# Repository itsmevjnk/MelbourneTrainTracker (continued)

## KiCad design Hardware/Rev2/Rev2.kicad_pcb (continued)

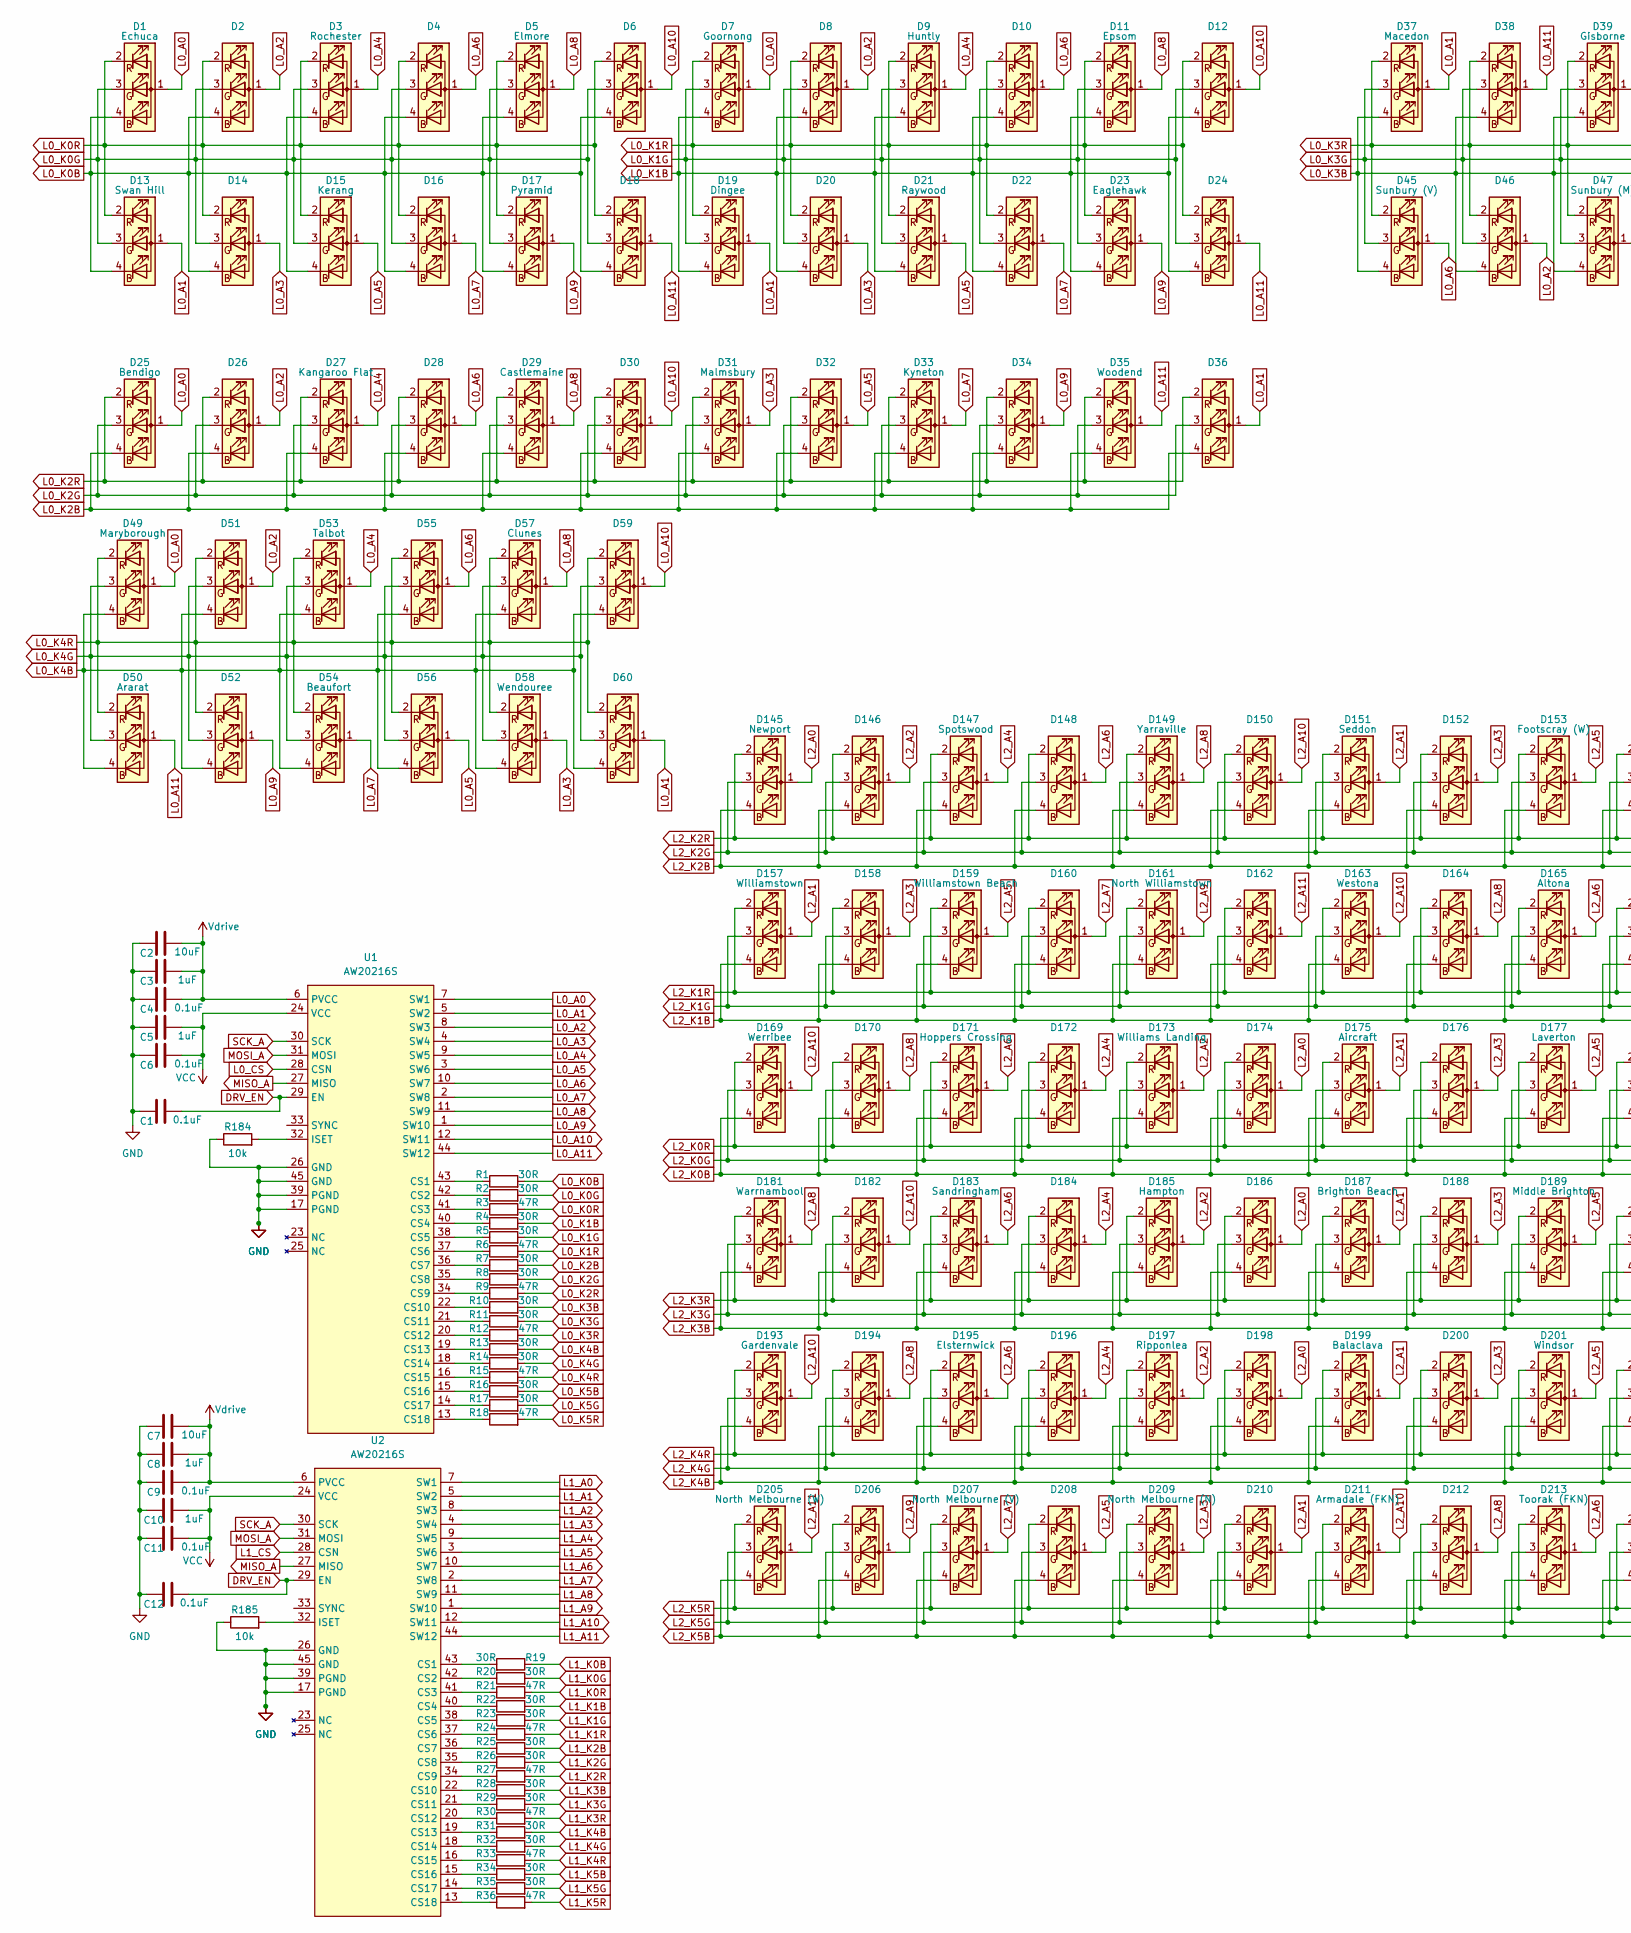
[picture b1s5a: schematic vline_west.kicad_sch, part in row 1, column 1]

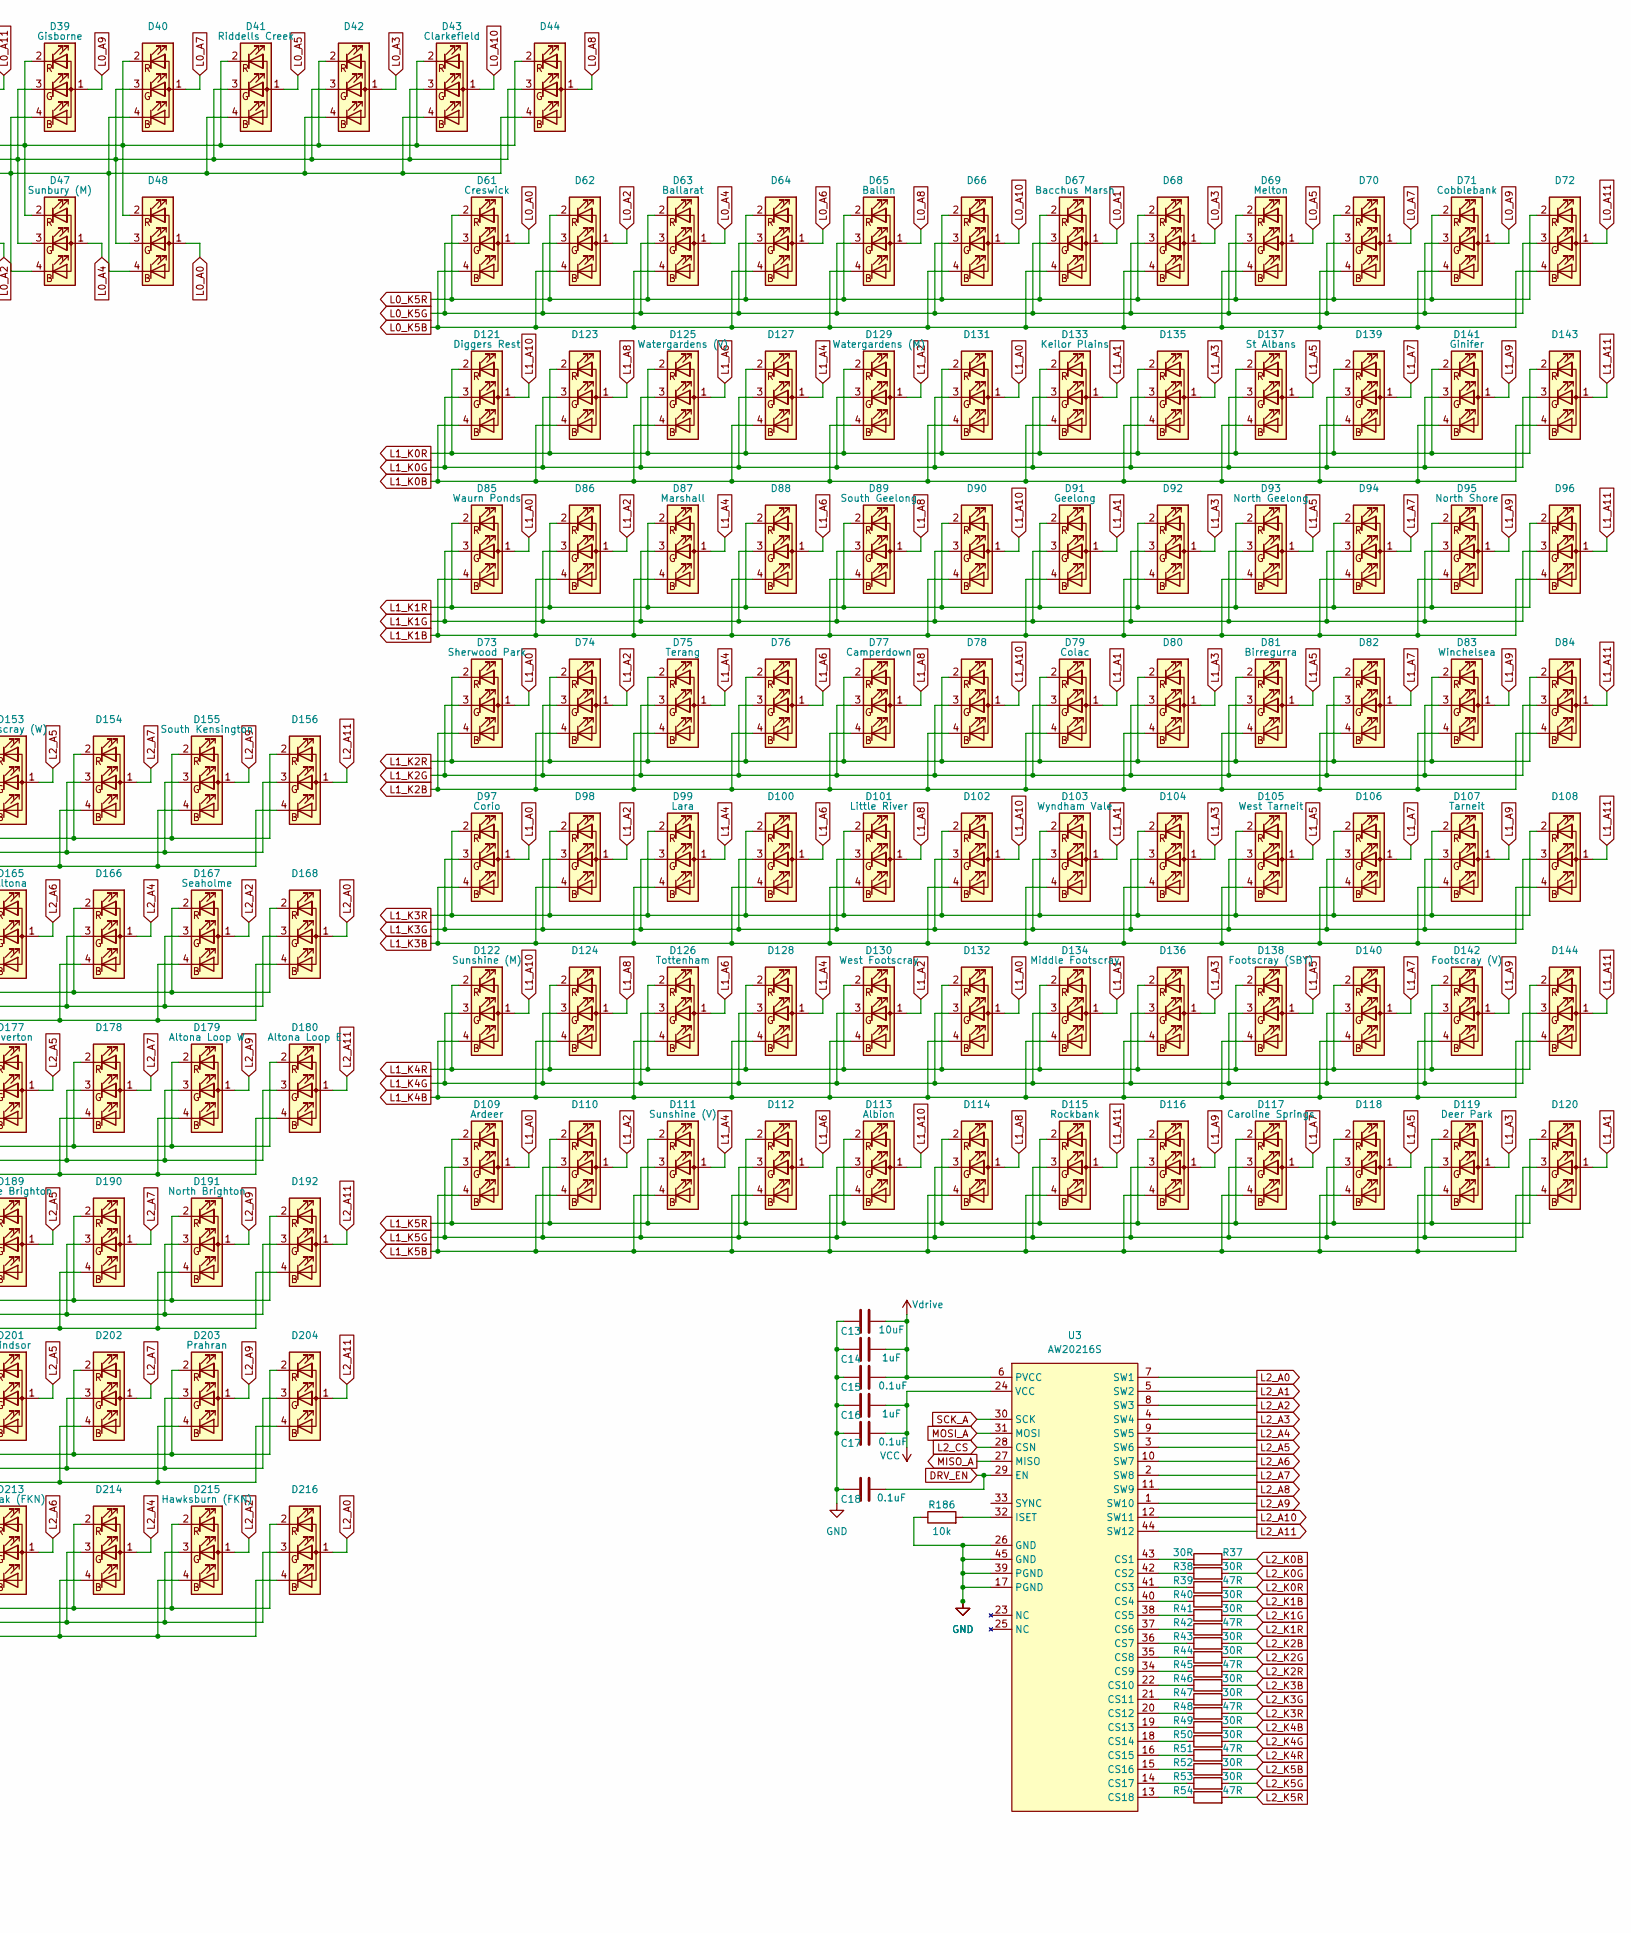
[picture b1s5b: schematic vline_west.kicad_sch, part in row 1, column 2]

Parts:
C1, C4, C6, C9, C11, C12, C15, C17, C18: 0.1uF; C_0603_1608Metric_Pad1.08x0.95mm_HandSolder; MPN C14663
C2, C7, C13: 10uF; C_0805_2012Metric_Pad1.18x1.45mm_HandSolder; MPN C380332
C3, C5, C8, C10, C14, C16: 1uF; C_0603_1608Metric_Pad1.08x0.95mm_HandSolder; MPN C6119849
D1, D2, D3, D4, D5, D6, D7, D8, D9, D10, D11, D12, D13, D14, D15, D16, D17, D18, D19, D20, D21, D22, D23, D24, D25, D26, D27, D28, D29, D30, D31, D32, D33, D34, D35, D36, D37, D38, D39, D40, D41, D42, D43, D44, D45, D46, D47, D48, D49, D50, D51, D52, D53, D54, D55, D56, D57, D58, D59, D60, D61, D62, D63, D64, D65, D66, D67, D68, D69, D70, D71, D72, D73, D74, D75, D76, D77, D78, D79, D80, D81, D82, D83, D84, D85, D86, D87, D88, D89, D90, D91, D92, D93, D94, D95, D96, D97, D98, D99, D100, D101, D102, D103, D104, D105, D106, D107, D108, D109, D110, D111, D112, D113, D114, D115, D116, D117, D118, D119, D120, D121, D122, D123, D124, D125, D126, D127, D128, D129, D130, D131, D132, D133, D134, D135, D136, D137, D138, D139, D140, D141, D142, D143, D144, D145, D146, D147, D148, D149, D150, D151, D152, D153, D154, D155, D156, D157, D158, D159, D160, D161, D162, D163, D164, D165, D166, D167, D168, D169, D170, D171, D172, D173, D174, D175, D176, D177, D178, D179, D180, D181, D182, D183, D184, D185, D186, D187, D188, D189, D190, D191, D192, D193, D194, D195, D196, D197, D198, D199, D200, D201, D202, D203, D204, D205, D206, D207, D208, D209, D210, D211, D212, D213, D214, D215, D216: XL-B1010RGBT-HF; LED_RGB_Xinglight-1010; MPN C22464515
R1, R2, R4, R5, R7, R8, R10, R11, R13, R14, R16, R17, R19, R20, R22, R23, R25, R26, R28, R29, R31, R32, R34, R35, R37, R38, R40, R41, R43, R44, R46, R47, R49, R50, R52, R53: 30R; R_0805_2012Metric_Pad1.20x1.40mm_HandSolder
R3, R6, R9, R12, R15, R18, R21, R24, R27, R30, R33, R36, R39, R42, R45, R48, R51, R54: 47R; R_0805_2012Metric_Pad1.20x1.40mm_HandSolder
R184, R185, R186: 10k; R_0603_1608Metric_Pad0.98x0.95mm_HandSolder; MPN C15401
U1, U2, U3: AW20216S; QFN-44-1EP_5x5mm_P0.4mm_EP2.45x2.45mm; MPN C7385556

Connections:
+3.3V: C5.2, C6.2, C10.2, C11.2, C16.2, C17.2, U1.24 (VCC), U2.24 (VCC), U3.24 (VCC); also elsewhere on the board
+5V: C2.2, C3.2, C4.2, C7.2, C8.2, C9.2, C13.2, C14.2, C15.2, U1.6 (PVCC), U2.6 (PVCC), U3.6 (PVCC); also elsewhere on the board
DRV_EN: C1.2, C12.2, C18.2, U1.29 (EN), U2.29 (EN), U3.29 (EN); also elsewhere on the board
GND: C1.1, C2.1, C3.1, C4.1, C5.1, C6.1, C7.1, C8.1, C9.1, C10.1, C11.1, C12.1, C13.1, C14.1, C15.1, C16.1, C17.1, C18.1, R184.1, R185.1, R186.1, U1.17 (PGND), U1.26 (GND), U1.39 (PGND), U1.45 (GND), U2.17 (PGND), U2.26 (GND), U2.39 (PGND), U2.45 (GND), U3.17 (PGND), U3.26 (GND), U3.39 (PGND), U3.45 (GND); also elsewhere on the board
L0_A0: D1.1 (A), D7.1 (A), D25.1 (A), D48.1 (A), D49.1 (A), D61.1 (A), U1.7 (SW1)
L0_A1: D13.1 (A), D19.1 (A), D36.1 (A), D37.1 (A), D60.1 (A), D67.1 (A), U1.5 (SW2)
L0_A2: D2.1 (A), D8.1 (A), D26.1 (A), D46.1 (A), D51.1 (A), D62.1 (A), U1.8 (SW3)
L0_A3: D14.1 (A), D20.1 (A), D31.1 (A), D42.1 (A), D58.1 (A), D68.1 (A), U1.4 (SW4)
L0_A4: D3.1 (A), D9.1 (A), D27.1 (A), D47.1 (A), D53.1 (A), D63.1 (A), U1.9 (SW5)
L0_A5: D15.1 (A), D21.1 (A), D32.1 (A), D41.1 (A), D56.1 (A), D69.1 (A), U1.3 (SW6)
L0_A6: D4.1 (A), D10.1 (A), D28.1 (A), D45.1 (A), D55.1 (A), D64.1 (A), U1.10 (SW7)
L0_A7: D16.1 (A), D22.1 (A), D33.1 (A), D40.1 (A), D54.1 (A), D70.1 (A), U1.2 (SW8)
L0_A8: D5.1 (A), D11.1 (A), D29.1 (A), D44.1 (A), D57.1 (A), D65.1 (A), U1.11 (SW9)
L0_A9: D17.1 (A), D23.1 (A), D34.1 (A), D39.1 (A), D52.1 (A), D71.1 (A), U1.1 (SW10)
L0_A10: D6.1 (A), D12.1 (A), D30.1 (A), D43.1 (A), D59.1 (A), D66.1 (A), U1.12 (SW11)
L0_A11: D18.1 (A), D24.1 (A), D35.1 (A), D38.1 (A), D50.1 (A), D72.1 (A), U1.44 (SW12)
L0_CS: U1.28 (CSN); also elsewhere on the board
L0_K0B: D1.4 (BK), D2.4 (BK), D3.4 (BK), D4.4 (BK), D5.4 (BK), D6.4 (BK), D13.4 (BK), D14.4 (BK), D15.4 (BK), D16.4 (BK), D17.4 (BK), D18.4 (BK), R1.2
L0_K0G: D1.3 (GK), D2.3 (GK), D3.3 (GK), D4.3 (GK), D5.3 (GK), D6.3 (GK), D13.3 (GK), D14.3 (GK), D15.3 (GK), D16.3 (GK), D17.3 (GK), D18.3 (GK), R2.2
L0_K0R: D1.2 (RK), D2.2 (RK), D3.2 (RK), D4.2 (RK), D5.2 (RK), D6.2 (RK), D13.2 (RK), D14.2 (RK), D15.2 (RK), D16.2 (RK), D17.2 (RK), D18.2 (RK), R3.2
L0_K1B: D7.4 (BK), D8.4 (BK), D9.4 (BK), D10.4 (BK), D11.4 (BK), D12.4 (BK), D19.4 (BK), D20.4 (BK), D21.4 (BK), D22.4 (BK), D23.4 (BK), D24.4 (BK), R4.2
L0_K1G: D7.3 (GK), D8.3 (GK), D9.3 (GK), D10.3 (GK), D11.3 (GK), D12.3 (GK), D19.3 (GK), D20.3 (GK), D21.3 (GK), D22.3 (GK), D23.3 (GK), D24.3 (GK), R5.2
L0_K1R: D7.2 (RK), D8.2 (RK), D9.2 (RK), D10.2 (RK), D11.2 (RK), D12.2 (RK), D19.2 (RK), D20.2 (RK), D21.2 (RK), D22.2 (RK), D23.2 (RK), D24.2 (RK), R6.2
L0_K2B: D25.4 (BK), D26.4 (BK), D27.4 (BK), D28.4 (BK), D29.4 (BK), D30.4 (BK), D31.4 (BK), D32.4 (BK), D33.4 (BK), D34.4 (BK), D35.4 (BK), D36.4 (BK), R7.2
L0_K2G: D25.3 (GK), D26.3 (GK), D27.3 (GK), D28.3 (GK), D29.3 (GK), D30.3 (GK), D31.3 (GK), D32.3 (GK), D33.3 (GK), D34.3 (GK), D35.3 (GK), D36.3 (GK), R8.2
L0_K2R: D25.2 (RK), D26.2 (RK), D27.2 (RK), D28.2 (RK), D29.2 (RK), D30.2 (RK), D31.2 (RK), D32.2 (RK), D33.2 (RK), D34.2 (RK), D35.2 (RK), D36.2 (RK), R9.2
L0_K3B: D37.4 (BK), D38.4 (BK), D39.4 (BK), D40.4 (BK), D41.4 (BK), D42.4 (BK), D43.4 (BK), D44.4 (BK), D45.4 (BK), D46.4 (BK), D47.4 (BK), D48.4 (BK), R10.2
L0_K3G: D37.3 (GK), D38.3 (GK), D39.3 (GK), D40.3 (GK), D41.3 (GK), D42.3 (GK), D43.3 (GK), D44.3 (GK), D45.3 (GK), D46.3 (GK), D47.3 (GK), D48.3 (GK), R11.2
L0_K3R: D37.2 (RK), D38.2 (RK), D39.2 (RK), D40.2 (RK), D41.2 (RK), D42.2 (RK), D43.2 (RK), D44.2 (RK), D45.2 (RK), D46.2 (RK), D47.2 (RK), D48.2 (RK), R12.2
L0_K4B: D49.4 (BK), D50.4 (BK), D51.4 (BK), D52.4 (BK), D53.4 (BK), D54.4 (BK), D55.4 (BK), D56.4 (BK), D57.4 (BK), D58.4 (BK), D59.4 (BK), D60.4 (BK), R13.2
L0_K4G: D49.3 (GK), D50.3 (GK), D51.3 (GK), D52.3 (GK), D53.3 (GK), D54.3 (GK), D55.3 (GK), D56.3 (GK), D57.3 (GK), D58.3 (GK), D59.3 (GK), D60.3 (GK), R14.2
L0_K4R: D49.2 (RK), D50.2 (RK), D51.2 (RK), D52.2 (RK), D53.2 (RK), D54.2 (RK), D55.2 (RK), D56.2 (RK), D57.2 (RK), D58.2 (RK), D59.2 (RK), D60.2 (RK), R15.2
L0_K5B: D61.4 (BK), D62.4 (BK), D63.4 (BK), D64.4 (BK), D65.4 (BK), D66.4 (BK), D67.4 (BK), D68.4 (BK), D69.4 (BK), D70.4 (BK), D71.4 (BK), D72.4 (BK), R16.2
L0_K5G: D61.3 (GK), D62.3 (GK), D63.3 (GK), D64.3 (GK), D65.3 (GK), D66.3 (GK), D67.3 (GK), D68.3 (GK), D69.3 (GK), D70.3 (GK), D71.3 (GK), D72.3 (GK), R17.2
L0_K5R: D61.2 (RK), D62.2 (RK), D63.2 (RK), D64.2 (RK), D65.2 (RK), D66.2 (RK), D67.2 (RK), D68.2 (RK), D69.2 (RK), D70.2 (RK), D71.2 (RK), D72.2 (RK), R18.2
L1_A0: D73.1 (A), D85.1 (A), D97.1 (A), D109.1 (A), D131.1 (A), D132.1 (A), U2.7 (SW1)
L1_A1: D79.1 (A), D91.1 (A), D103.1 (A), D120.1 (A), D133.1 (A), D134.1 (A), U2.5 (SW2)
L1_A2: D74.1 (A), D86.1 (A), D98.1 (A), D110.1 (A), D129.1 (A), D130.1 (A), U2.8 (SW3)
L1_A3: D80.1 (A), D92.1 (A), D104.1 (A), D119.1 (A), D135.1 (A), D136.1 (A), U2.4 (SW4)
L1_A4: D75.1 (A), D87.1 (A), D99.1 (A), D111.1 (A), D127.1 (A), D128.1 (A), U2.9 (SW5)
L1_A5: D81.1 (A), D93.1 (A), D105.1 (A), D118.1 (A), D137.1 (A), D138.1 (A), U2.3 (SW6)
L1_A6: D76.1 (A), D88.1 (A), D100.1 (A), D112.1 (A), D125.1 (A), D126.1 (A), U2.10 (SW7)
L1_A7: D82.1 (A), D94.1 (A), D106.1 (A), D117.1 (A), D139.1 (A), D140.1 (A), U2.2 (SW8)
L1_A8: D77.1 (A), D89.1 (A), D101.1 (A), D114.1 (A), D123.1 (A), D124.1 (A), U2.11 (SW9)
L1_A9: D83.1 (A), D95.1 (A), D107.1 (A), D116.1 (A), D141.1 (A), D142.1 (A), U2.1 (SW10)
L1_A10: D78.1 (A), D90.1 (A), D102.1 (A), D113.1 (A), D121.1 (A), D122.1 (A), U2.12 (SW11)
L1_A11: D84.1 (A), D96.1 (A), D108.1 (A), D115.1 (A), D143.1 (A), D144.1 (A), U2.44 (SW12)
L1_CS: U2.28 (CSN); also elsewhere on the board
L1_K0B: D121.4 (BK), D123.4 (BK), D125.4 (BK), D127.4 (BK), D129.4 (BK), D131.4 (BK), D133.4 (BK), D135.4 (BK), D137.4 (BK), D139.4 (BK), D141.4 (BK), D143.4 (BK), R19.1
L1_K0G: D121.3 (GK), D123.3 (GK), D125.3 (GK), D127.3 (GK), D129.3 (GK), D131.3 (GK), D133.3 (GK), D135.3 (GK), D137.3 (GK), D139.3 (GK), D141.3 (GK), D143.3 (GK), R20.2
L1_K0R: D121.2 (RK), D123.2 (RK), D125.2 (RK), D127.2 (RK), D129.2 (RK), D131.2 (RK), D133.2 (RK), D135.2 (RK), D137.2 (RK), D139.2 (RK), D141.2 (RK), D143.2 (RK), R21.2
L1_K1B: D85.4 (BK), D86.4 (BK), D87.4 (BK), D88.4 (BK), D89.4 (BK), D90.4 (BK), D91.4 (BK), D92.4 (BK), D93.4 (BK), D94.4 (BK), D95.4 (BK), D96.4 (BK), R22.2
L1_K1G: D85.3 (GK), D86.3 (GK), D87.3 (GK), D88.3 (GK), D89.3 (GK), D90.3 (GK), D91.3 (GK), D92.3 (GK), D93.3 (GK), D94.3 (GK), D95.3 (GK), D96.3 (GK), R23.2
L1_K1R: D85.2 (RK), D86.2 (RK), D87.2 (RK), D88.2 (RK), D89.2 (RK), D90.2 (RK), D91.2 (RK), D92.2 (RK), D93.2 (RK), D94.2 (RK), D95.2 (RK), D96.2 (RK), R24.2
L1_K2B: D73.4 (BK), D74.4 (BK), D75.4 (BK), D76.4 (BK), D77.4 (BK), D78.4 (BK), D79.4 (BK), D80.4 (BK), D81.4 (BK), D82.4 (BK), D83.4 (BK), D84.4 (BK), R25.2
L1_K2G: D73.3 (GK), D74.3 (GK), D75.3 (GK), D76.3 (GK), D77.3 (GK), D78.3 (GK), D79.3 (GK), D80.3 (GK), D81.3 (GK), D82.3 (GK), D83.3 (GK), D84.3 (GK), R26.2
L1_K2R: D73.2 (RK), D74.2 (RK), D75.2 (RK), D76.2 (RK), D77.2 (RK), D78.2 (RK), D79.2 (RK), D80.2 (RK), D81.2 (RK), D82.2 (RK), D83.2 (RK), D84.2 (RK), R27.2
L1_K3B: D97.4 (BK), D98.4 (BK), D99.4 (BK), D100.4 (BK), D101.4 (BK), D102.4 (BK), D103.4 (BK), D104.4 (BK), D105.4 (BK), D106.4 (BK), D107.4 (BK), D108.4 (BK), R28.2
L1_K3G: D97.3 (GK), D98.3 (GK), D99.3 (GK), D100.3 (GK), D101.3 (GK), D102.3 (GK), D103.3 (GK), D104.3 (GK), D105.3 (GK), D106.3 (GK), D107.3 (GK), D108.3 (GK), R29.2
L1_K3R: D97.2 (RK), D98.2 (RK), D99.2 (RK), D100.2 (RK), D101.2 (RK), D102.2 (RK), D103.2 (RK), D104.2 (RK), D105.2 (RK), D106.2 (RK), D107.2 (RK), D108.2 (RK), R30.2
L1_K4B: D122.4 (BK), D124.4 (BK), D126.4 (BK), D128.4 (BK), D130.4 (BK), D132.4 (BK), D134.4 (BK), D136.4 (BK), D138.4 (BK), D140.4 (BK), D142.4 (BK), D144.4 (BK), R31.2
L1_K4G: D122.3 (GK), D124.3 (GK), D126.3 (GK), D128.3 (GK), D130.3 (GK), D132.3 (GK), D134.3 (GK), D136.3 (GK), D138.3 (GK), D140.3 (GK), D142.3 (GK), D144.3 (GK), R32.2
L1_K4R: D122.2 (RK), D124.2 (RK), D126.2 (RK), D128.2 (RK), D130.2 (RK), D132.2 (RK), D134.2 (RK), D136.2 (RK), D138.2 (RK), D140.2 (RK), D142.2 (RK), D144.2 (RK), R33.2
L1_K5B: D109.4 (BK), D110.4 (BK), D111.4 (BK), D112.4 (BK), D113.4 (BK), D114.4 (BK), D115.4 (BK), D116.4 (BK), D117.4 (BK), D118.4 (BK), D119.4 (BK), D120.4 (BK), R34.2
L1_K5G: D109.3 (GK), D110.3 (GK), D111.3 (GK), D112.3 (GK), D113.3 (GK), D114.3 (GK), D115.3 (GK), D116.3 (GK), D117.3 (GK), D118.3 (GK), D119.3 (GK), D120.3 (GK), R35.2
L1_K5R: D109.2 (RK), D110.2 (RK), D111.2 (RK), D112.2 (RK), D113.2 (RK), D114.2 (RK), D115.2 (RK), D116.2 (RK), D117.2 (RK), D118.2 (RK), D119.2 (RK), D120.2 (RK), R36.2
L2_A0: D145.1 (A), D168.1 (A), D174.1 (A), D186.1 (A), D198.1 (A), D216.1 (A), U3.7 (SW1)
L2_A1: D151.1 (A), D157.1 (A), D175.1 (A), D187.1 (A), D199.1 (A), D210.1 (A), U3.5 (SW2)
L2_A2: D146.1 (A), D167.1 (A), D173.1 (A), D185.1 (A), D197.1 (A), D215.1 (A), U3.8 (SW3)
L2_A3: D152.1 (A), D158.1 (A), D176.1 (A), D188.1 (A), D200.1 (A), D209.1 (A), U3.4 (SW4)
L2_A4: D147.1 (A), D166.1 (A), D172.1 (A), D184.1 (A), D196.1 (A), D214.1 (A), U3.9 (SW5)
L2_A5: D153.1 (A), D159.1 (A), D177.1 (A), D189.1 (A), D201.1 (A), D208.1 (A), U3.3 (SW6)
L2_A6: D148.1 (A), D165.1 (A), D171.1 (A), D183.1 (A), D195.1 (A), D213.1 (A), U3.10 (SW7)
L2_A7: D154.1 (A), D160.1 (A), D178.1 (A), D190.1 (A), D202.1 (A), D207.1 (A), U3.2 (SW8)
L2_A8: D149.1 (A), D164.1 (A), D170.1 (A), D181.1 (A), D194.1 (A), D212.1 (A), U3.11 (SW9)
L2_A9: D155.1 (A), D161.1 (A), D179.1 (A), D191.1 (A), D203.1 (A), D206.1 (A), U3.1 (SW10)
L2_A10: D150.1 (A), D163.1 (A), D169.1 (A), D182.1 (A), D193.1 (A), D211.1 (A), U3.12 (SW11)
L2_A11: D156.1 (A), D162.1 (A), D180.1 (A), D192.1 (A), D204.1 (A), D205.1 (A), U3.44 (SW12)
L2_CS: U3.28 (CSN); also elsewhere on the board
L2_K0B: D169.4 (BK), D170.4 (BK), D171.4 (BK), D172.4 (BK), D173.4 (BK), D174.4 (BK), D175.4 (BK), D176.4 (BK), D177.4 (BK), D178.4 (BK), D179.4 (BK), D180.4 (BK), R37.1
L2_K0G: D169.3 (GK), D170.3 (GK), D171.3 (GK), D172.3 (GK), D173.3 (GK), D174.3 (GK), D175.3 (GK), D176.3 (GK), D177.3 (GK), D178.3 (GK), D179.3 (GK), D180.3 (GK), R38.2
L2_K0R: D169.2 (RK), D170.2 (RK), D171.2 (RK), D172.2 (RK), D173.2 (RK), D174.2 (RK), D175.2 (RK), D176.2 (RK), D177.2 (RK), D178.2 (RK), D179.2 (RK), D180.2 (RK), R39.2
L2_K1B: D157.4 (BK), D158.4 (BK), D159.4 (BK), D160.4 (BK), D161.4 (BK), D162.4 (BK), D163.4 (BK), D164.4 (BK), D165.4 (BK), D166.4 (BK), D167.4 (BK), D168.4 (BK), R40.2
L2_K1G: D157.3 (GK), D158.3 (GK), D159.3 (GK), D160.3 (GK), D161.3 (GK), D162.3 (GK), D163.3 (GK), D164.3 (GK), D165.3 (GK), D166.3 (GK), D167.3 (GK), D168.3 (GK), R41.2
L2_K1R: D157.2 (RK), D158.2 (RK), D159.2 (RK), D160.2 (RK), D161.2 (RK), D162.2 (RK), D163.2 (RK), D164.2 (RK), D165.2 (RK), D166.2 (RK), D167.2 (RK), D168.2 (RK), R42.2
L2_K2B: D145.4 (BK), D146.4 (BK), D147.4 (BK), D148.4 (BK), D149.4 (BK), D150.4 (BK), D151.4 (BK), D152.4 (BK), D153.4 (BK), D154.4 (BK), D155.4 (BK), D156.4 (BK), R43.2
L2_K2G: D145.3 (GK), D146.3 (GK), D147.3 (GK), D148.3 (GK), D149.3 (GK), D150.3 (GK), D151.3 (GK), D152.3 (GK), D153.3 (GK), D154.3 (GK), D155.3 (GK), D156.3 (GK), R44.2
L2_K2R: D145.2 (RK), D146.2 (RK), D147.2 (RK), D148.2 (RK), D149.2 (RK), D150.2 (RK), D151.2 (RK), D152.2 (RK), D153.2 (RK), D154.2 (RK), D155.2 (RK), D156.2 (RK), R45.2
L2_K3B: D181.4 (BK), D182.4 (BK), D183.4 (BK), D184.4 (BK), D185.4 (BK), D186.4 (BK), D187.4 (BK), D188.4 (BK), D189.4 (BK), D190.4 (BK), D191.4 (BK), D192.4 (BK), R46.2
L2_K3G: D181.3 (GK), D182.3 (GK), D183.3 (GK), D184.3 (GK), D185.3 (GK), D186.3 (GK), D187.3 (GK), D188.3 (GK), D189.3 (GK), D190.3 (GK), D191.3 (GK), D192.3 (GK), R47.2
L2_K3R: D181.2 (RK), D182.2 (RK), D183.2 (RK), D184.2 (RK), D185.2 (RK), D186.2 (RK), D187.2 (RK), D188.2 (RK), D189.2 (RK), D190.2 (RK), D191.2 (RK), D192.2 (RK), R48.2
L2_K4B: D193.4 (BK), D194.4 (BK), D195.4 (BK), D196.4 (BK), D197.4 (BK), D198.4 (BK), D199.4 (BK), D200.4 (BK), D201.4 (BK), D202.4 (BK), D203.4 (BK), D204.4 (BK), R49.2
L2_K4G: D193.3 (GK), D194.3 (GK), D195.3 (GK), D196.3 (GK), D197.3 (GK), D198.3 (GK), D199.3 (GK), D200.3 (GK), D201.3 (GK), D202.3 (GK), D203.3 (GK), D204.3 (GK), R50.2
L2_K4R: D193.2 (RK), D194.2 (RK), D195.2 (RK), D196.2 (RK), D197.2 (RK), D198.2 (RK), D199.2 (RK), D200.2 (RK), D201.2 (RK), D202.2 (RK), D203.2 (RK), D204.2 (RK), R51.2
L2_K5B: D205.4 (BK), D206.4 (BK), D207.4 (BK), D208.4 (BK), D209.4 (BK), D210.4 (BK), D211.4 (BK), D212.4 (BK), D213.4 (BK), D214.4 (BK), D215.4 (BK), D216.4 (BK), R52.2
L2_K5G: D205.3 (GK), D206.3 (GK), D207.3 (GK), D208.3 (GK), D209.3 (GK), D210.3 (GK), D211.3 (GK), D212.3 (GK), D213.3 (GK), D214.3 (GK), D215.3 (GK), D216.3 (GK), R53.2
L2_K5R: D205.2 (RK), D206.2 (RK), D207.2 (RK), D208.2 (RK), D209.2 (RK), D210.2 (RK), D211.2 (RK), D212.2 (RK), D213.2 (RK), D214.2 (RK), D215.2 (RK), D216.2 (RK), R54.2
MISO_A: U1.27 (MISO), U2.27 (MISO), U3.27 (MISO); also elsewhere on the board
MOSI_A: U1.31 (MOSI), U2.31 (MOSI), U3.31 (MOSI); also elsewhere on the board
unnamed: R1.1, U1.43 (CS1)
unnamed: R2.1, U1.42 (CS2)
unnamed: R3.1, U1.41 (CS3)
unnamed: R4.1, U1.40 (CS4)
unnamed: R5.1, U1.38 (CS5)
unnamed: R6.1, U1.37 (CS6)
unnamed: R7.1, U1.36 (CS7)
unnamed: R8.1, U1.35 (CS8)
unnamed: R9.1, U1.34 (CS9)
unnamed: R10.1, U1.22 (CS10)
unnamed: R11.1, U1.21 (CS11)
unnamed: R12.1, U1.20 (CS12)
unnamed: R13.1, U1.19 (CS13)
unnamed: R14.1, U1.18 (CS14)
unnamed: R15.1, U1.16 (CS15)
unnamed: R16.1, U1.15 (CS16)
unnamed: R17.1, U1.14 (CS17)
unnamed: R18.1, U1.13 (CS18)
unnamed: R184.2, U1.32 (ISET)
unnamed: R19.2, U2.43 (CS1)
unnamed: R20.1, U2.42 (CS2)
unnamed: R21.1, U2.41 (CS3)
unnamed: R22.1, U2.40 (CS4)
unnamed: R23.1, U2.38 (CS5)
unnamed: R24.1, U2.37 (CS6)
unnamed: R25.1, U2.36 (CS7)
unnamed: R26.1, U2.35 (CS8)
unnamed: R27.1, U2.34 (CS9)
unnamed: R28.1, U2.22 (CS10)
unnamed: R29.1, U2.21 (CS11)
unnamed: R30.1, U2.20 (CS12)
unnamed: R31.1, U2.19 (CS13)
unnamed: R32.1, U2.18 (CS14)
unnamed: R33.1, U2.16 (CS15)
unnamed: R34.1, U2.15 (CS16)
unnamed: R35.1, U2.14 (CS17)
unnamed: R36.1, U2.13 (CS18)
unnamed: R185.2, U2.32 (ISET)
unnamed: R37.2, U3.43 (CS1)
unnamed: R38.1, U3.42 (CS2)
unnamed: R39.1, U3.41 (CS3)
unnamed: R40.1, U3.40 (CS4)
unnamed: R41.1, U3.38 (CS5)
unnamed: R42.1, U3.37 (CS6)
unnamed: R43.1, U3.36 (CS7)
unnamed: R44.1, U3.35 (CS8)
unnamed: R45.1, U3.34 (CS9)
unnamed: R46.1, U3.22 (CS10)
unnamed: R47.1, U3.21 (CS11)
unnamed: R48.1, U3.20 (CS12)
unnamed: R49.1, U3.19 (CS13)
unnamed: R50.1, U3.18 (CS14)
unnamed: R51.1, U3.16 (CS15)
unnamed: R52.1, U3.15 (CS16)
unnamed: R53.1, U3.14 (CS17)
unnamed: R54.1, U3.13 (CS18)
unnamed: R186.2, U3.32 (ISET)
SCK_A: U1.30 (SCK), U2.30 (SCK), U3.30 (SCK); also elsewhere on the board

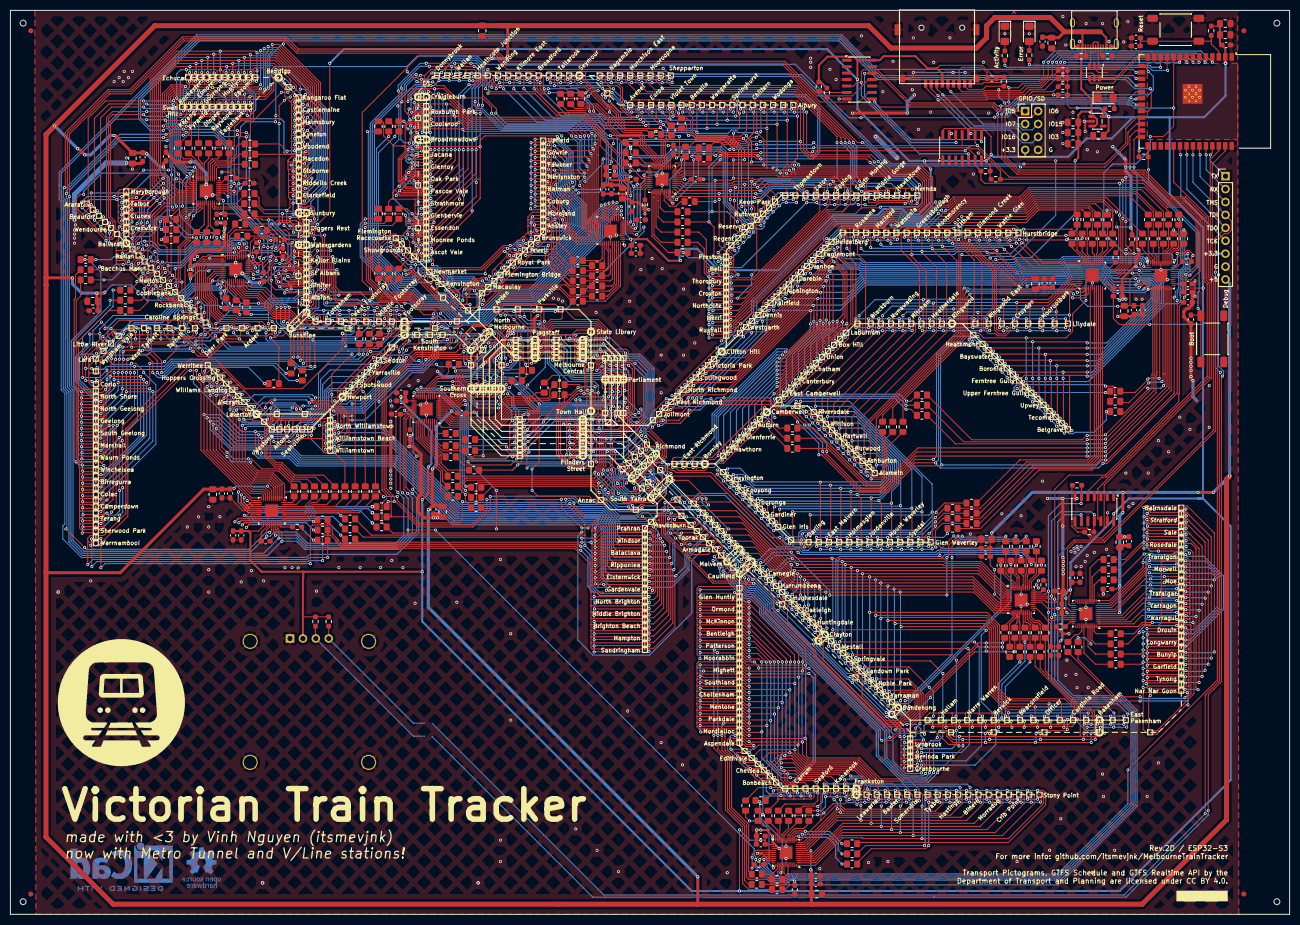
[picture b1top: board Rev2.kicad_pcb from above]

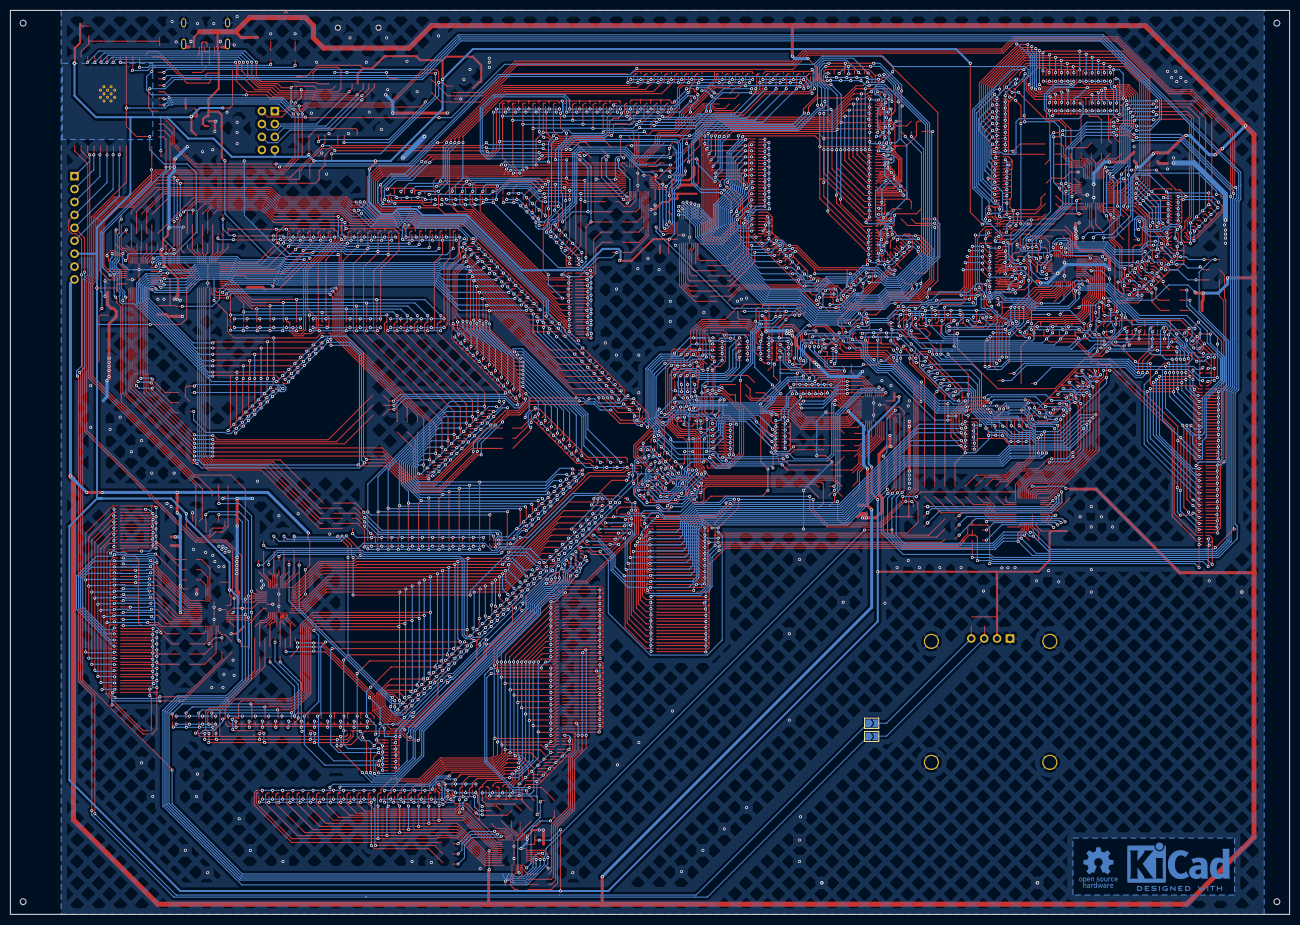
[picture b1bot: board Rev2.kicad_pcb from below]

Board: 2 copper layers, 251.6 x 177.8 mm, 1060 parts (2 on the bottom side), 570 nets.

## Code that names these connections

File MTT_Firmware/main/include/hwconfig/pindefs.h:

/* pin definitions */

#pragma once

#include <driver/gpio.h>
#include <driver/spi_master.h>

#define BTN_BOOT                        GPIO_NUM_0 // BOOT button

#if CONFIG_IDF_TARGET_ESP32S3

/* SPI buses */
#define SPI3_MISO                       GPIO_NUM_13
#define SPI3_MOSI                       GPIO_NUM_11
#define SPI3_SCK                        GPIO_NUM_12

/* LED drivers */
#define L0_SPI                          SPI3_HOST
#define L0_CS                           GPIO_NUM_10
#define L1_SPI                          SPI3_HOST
#define L1_CS                           GPIO_NUM_14
#define L2_SPI                          SPI3_HOST
#define L2_CS                           GPIO_NUM_9
#define L3_SPI                          SPI3_HOST
#define L3_CS                           GPIO_NUM_46
#define L4_SPI                          SPI3_HOST
#define L4_CS                           GPIO_NUM_21
#define L5_SPI                          SPI3_HOST
#define L5_CS                           GPIO_NUM_47
#define L6_SPI                          SPI3_HOST
#define L6_CS                           GPIO_NUM_48
#define L7_SPI                          SPI3_HOST
#define L7_CS                           GPIO_NUM_45
#define L8_SPI                          SPI3_HOST
#define L8_CS                           GPIO_NUM_38
#define L9_SPI                          SPI3_HOST
#define L9_CS                           GPIO_NUM_1
#define L10_SPI                         SPI3_HOST
#define L10_CS                          GPIO_NUM_2

#define DRV_EN                          GPIO_NUM_17

/* status LEDs */
#define LED_ACTY                        GPIO_NUM_18
#define LED_ERROR                       GPIO_NUM_8

#define I2C_SCL                         GPIO_NUM_41
#define I2C_SDA                         GPIO_NUM_40

#else // original ESP32 revision

/* SPI buses */
#define SPI2_MISO                       GPIO_NUM_12
#define SPI2_MOSI                       GPIO_NUM_13
#define SPI2_SCK                        GPIO_NUM_14
#define SPI3_MISO                       GPIO_NUM_19
#define SPI3_MOSI                       GPIO_NUM_21
#define SPI3_SCK                        GPIO_NUM_18

/* LED drivers */
#define L0_SPI                          SPI2_HOST
#define L0_CS                           GPIO_NUM_4
#define L1_SPI                          SPI2_HOST
#define L1_CS                           GPIO_NUM_16
#define L2_SPI                          SPI2_HOST
#define L2_CS                           GPIO_NUM_17
#define L3_SPI                          SPI2_HOST
#define L3_CS                           GPIO_NUM_22
#define L4_SPI                          SPI3_HOST
#define L4_CS                           GPIO_NUM_23
#define L5_SPI                          SPI3_HOST
#define L5_CS                           GPIO_NUM_25
#define L6_SPI                          SPI3_HOST
#define L6_CS                           GPIO_NUM_26
#define L7_SPI                          SPI3_HOST
#define L7_CS                           GPIO_NUM_27

#define DRV_EN                          GPIO_NUM_32

/* status LEDs */
#define LED_ACTY                        GPIO_NUM_2
#define LED_ERROR                       GPIO_NUM_33

// #define CONFIG_SPI3_ONLY // only use SPI3 (VSPI), leaving HSPI for JTAG
#if defined(CONFIG_SPI3_ONLY)
#undef L0_SPI
#define L0_SPI SPI3_HOST
#undef L1_SPI
#define L1_SPI SPI3_HOST
#undef L2_SPI
#define L2_SPI SPI3_HOST
#undef L3_SPI
#define L3_SPI SPI3_HOST
#undef L4_SPI
#define L4_SPI SPI3_HOST
#undef L5_SPI
#define L5_SPI SPI3_HOST
#undef L6_SPI
#define L6_SPI SPI3_HOST
#undef L7_SPI
#define L7_SPI SPI3_HOST
#endif

#endif
